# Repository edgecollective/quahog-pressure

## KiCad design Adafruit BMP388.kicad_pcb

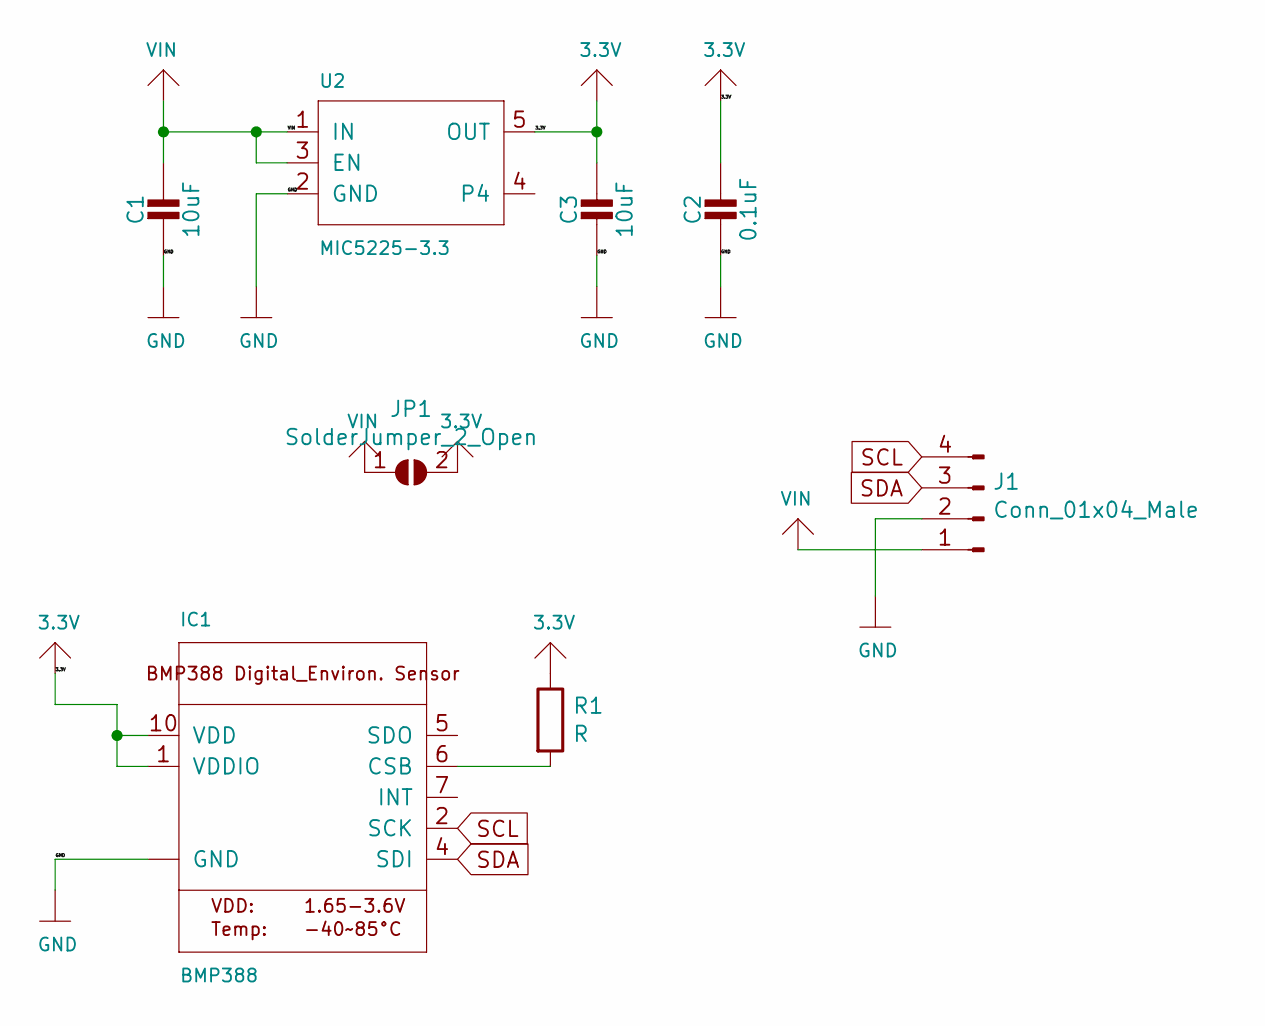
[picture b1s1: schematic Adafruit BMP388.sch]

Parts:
C1, C3: 10uF; C_0805_2012Metric_Pad1.15x1.40mm_HandSolder
C2: 0.1uF; C_0805_2012Metric_Pad1.15x1.40mm_HandSolder
IC1: BMP388
J1: Conn_01x04_Male; PinHeader_1x04_P2.54mm_Vertical
JP1: SolderJumper_2_Open; SolderJumper-2_P1.3mm_Open_RoundedPad1.0x1.5mm
R1: R; R_0805_2012Metric_Pad1.15x1.40mm_HandSolder
U2: MIC5225-3.3; SOT-23-5

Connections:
3.3V: C2.1, C3.1, IC1.1 (VDDIO), IC1.10 (VDD), JP1.2 (B), R1.1, U2.5 (OUT)
GND: C1.2, C2.2, C3.2, IC1.3 (GND), IC1.8 (GND), IC1.9 (GND), J1.2, U2.2 (GND)
unnamed: IC1.6 (CSB), R1.2
SCL: IC1.2 (SCK), J1.4
SDA: IC1.4 (SDI), J1.3
VIN: C1.1, J1.1, JP1.1 (A), U2.1 (IN), U2.3 (EN)

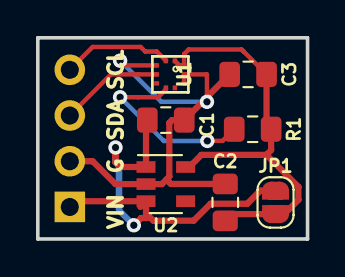
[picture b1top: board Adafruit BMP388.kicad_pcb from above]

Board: 2 copper layers, 15.0 x 11.2 mm, 8 parts (0 on the bottom side), 6 nets.

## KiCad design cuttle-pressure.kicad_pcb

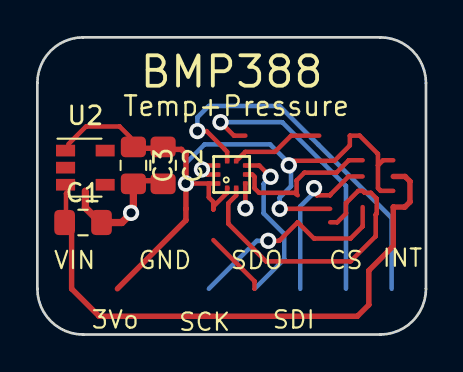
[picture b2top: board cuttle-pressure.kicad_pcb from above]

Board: 2 copper layers, 21.6 x 16.5 mm, 5 parts (0 on the bottom side), 3 nets.

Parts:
C1, C3: 10uF; C_0805_2012Metric_Pad1.15x1.40mm_HandSolder
C2: 0.1uF; C_0805_2012Metric_Pad1.15x1.40mm_HandSolder
IC1: BMP388
U2: MIC5225-3.3; SOT-23-5

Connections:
3.3V: C2.1, C3.1, IC1.1, IC1.6, IC1.10, U2.5
GND: C1.2, C2.2, C3.2, IC1.3, IC1.8, IC1.9, U2.2
VIN: C1.1, U2.1, U2.3
